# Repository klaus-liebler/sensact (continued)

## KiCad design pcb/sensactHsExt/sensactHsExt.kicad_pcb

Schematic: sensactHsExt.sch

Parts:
C1, C3, C4, C5, C6, C7, C8, C10, C12, C14, C16, C17: u1; C_0805_2012Metric_Pad1.15x1.40mm_HandSolder
C2, C9: 4u7; C_1206_3216Metric_Pad1.42x1.75mm_HandSolder
C11, C15: C; C_0805_2012Metric_Pad1.15x1.40mm_HandSolder
C13: m1; C_1206_3216Metric_Pad1.42x1.75mm_HandSolder
D1: LED; LED_0805_2012Metric_Pad1.15x1.40mm_HandSolder
D2: MBR0540; D_SOD-123
J1: B3; TestPoint_Pad_2.5x2.5mm
J2: LINKS1; PhoenixContact_MC_0,5_8-G-2.5_1x08_P2.50mm_Horizontal
J3, J7: SO8; SO-8_3.9x4.9mm_P1.27mm
J4: SensactBusConnector; IDC-Header_2x05_P2.54mm_Horizontal
J5: PROG; USB_Micro-B_Tensility_54-00023_Vertical
J6: LINKS2; PhoenixContact_MC_0,5_8-G-2.5_1x08_P2.50mm_Horizontal
J8: USB_C_Receptacle_USB2.0; USB_C_Receptacle_HRO_TYPE-C-31-M-12
J9: B4; TestPoint_Pad_2.5x2.5mm
J10: B5; TestPoint_Pad_2.5x2.5mm
J11: B6; TestPoint_Pad_2.5x2.5mm
J12: B7; TestPoint_Pad_2.5x2.5mm
J13: A15; TestPoint_Pad_2.5x2.5mm
J14: Conn_01x04; PhoenixContact_MC_0,5_4-G-2.5_1x04_P2.50mm_Horizontal
J15: P0A; TestPoint_Pad_2.5x2.5mm
J16: P0W; TestPoint_Pad_2.5x2.5mm
J17: P0B; TestPoint_Pad_2.5x2.5mm
J18: P1A; TestPoint_Pad_2.5x2.5mm
J19: P1W; TestPoint_Pad_2.5x2.5mm
J20: P1B; TestPoint_Pad_2.5x2.5mm
JP1: 3V3_INT; SolderJumper-2_P1.3mm_Open_Pad1.0x1.5mm
L1: 150u; L_Wuerth_HCI-7040
R1, R10, R12, R15, R16: R; R_0805_2012Metric_Pad1.15x1.40mm_HandSolder
R2: 10r; R_0805_2012Metric_Pad1.15x1.40mm_HandSolder
R3, R13: 3k3; R_0805_2012Metric_Pad1.15x1.40mm_HandSolder
R4: 2k2; R_0805_2012Metric_Pad1.15x1.40mm_HandSolder
R5, R6: 5k1; R_0805_2012Metric_Pad1.15x1.40mm_HandSolder
R7, R8, R9, R11, R14: 1k; R_0805_2012Metric_Pad1.15x1.40mm_HandSolder
R17: 10k; R_0805_2012Metric_Pad1.15x1.40mm_HandSolder
SW1: Reset; SW_SPST_CK_RS282G05A3
SW2: SW_Push; SW_Tactile_SPST_Angled_PTS645Vx83-2LFS
SW3: Mitsumi_SIQ-02FVS3
U1: FP-096H09A; FPC_TOP_1x08-1MP_P0.50mm_Horizontal
U2: STM32F072C8Tx; LQFP-48_7x7mm_P0.5mm_handsolder
U3: LMR14206; SOT-23-6
U4: SN65HVD230; SOIC-8_3.9x4.9mm_Pitch1.27mm_handsolder
U5: MCP42010; SOIC-14_3.9x8.7mm_P1.27mm_handsolder
Z9, Z10, Z11, Z12, Z13, Z14, Z15, Z16, Z17, Z18, Z19, Z20, Z21, Z22, Z23, Z24, Z25, Z26, Z27, Z28, Z29, Z30, Z31, Z32, Z33, Z34, Z35, Z36, Z37, Z38, Z39, Z40: StripRow3

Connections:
+3V3: C2.1, C3.1, C4.1, C5.1, C6.1, C7.1, C13.1, C14.1, C16.1, C17.1, JP1.2 (B), L1.1, R1.1, R7.1, R11.1, R12.2, R13.1, R15.1, U1.2 (VDD), U2.1 (VBAT), U2.9 (VDDA), U2.24 (VDD), U2.36 (VDDIO2), U2.48 (VDD), U4.3 (VCC), U5.12 (~SHDN), U5.14 (VDD); also elsewhere on the board
+24V: C9.1, J4.7 (24V), J4.8 (24V), J14.1, U3.5 (VIN); also elsewhere on the board
/CANH: J14.3, U4.7 (CANH)
/CANL: J14.4, U4.6 (CANL)
/CB: C12.2, U3.1 (CB)
/FB: R13.2, R14.1, U3.3 (FB)
/INT0: J4.4 (INT0), U2.19 (PB1)
/INT1: J4.5 (INT1), U2.18 (PB0)
/INT2: J4.6 (INT2), U2.14 (PA4)
/NRST: C1.1, SW1.1, U1.6 (~RESET), U2.7 (NRST), U5.11 (~RS)
/RX: J5.5 (GND), U2.31 (PA10)
/SCL: J4.2 (SCL), U2.21 (PB10)
/SDA: J4.3 (SDA), U2.22 (PB11)
/SW: C12.1, D2.1 (K), L1.2, U3.6 (SW)
/SWCLK: J5.1 (VBUS), U2.37 (PA14)
/SWDIO: J5.3 (D+), U2.34 (PA13)
/TX: J5.4 (ID), U2.30 (PA9)
/USB+: J8.A6 (D+), J8.B6 (D+), U2.33 (PA12)
/USB-: J8.A7 (D-), J8.B7 (D-), U2.32 (PA11)
CANR: U2.45 (PB8), U4.4 (R)
CANT: U2.46 (PB9), U4.1 (D)
GND: C1.2, C2.2, C3.2, C4.2, C5.2, C6.2, C7.2, C8.2, C9.2, C10.1, C11.2, C13.2, C14.2, C15.2, C16.2, C17.2, D2.2 (A), J4.9 (GND), J4.10 (GND), J5.2 (D-), J5.6 (Shield), J8.A1 (GND), J8.A12 (GND), J8.B1 (GND), J8.B12 (GND), J8.S1 (SHIELD), J14.2, R3.1, R5.1, R6.1, R14.2, R17.2, SW1.2, SW2.1, SW3.C, U1.7 (GND), U2.8 (VSSA), U2.23 (VSS), U2.35 (VSS), U2.44 (BOOT0), U2.47 (VSS), U3.2 (GND), U4.2 (GND), U5.4 (VSS); also elsewhere on the board
LCDBL: R2.2, U2.6 (PF1)
LCDCS: U1.1 (~CS), U2.16 (PA6)
LCDRS: U1.5 (RS), U2.13 (PA3)
LED: D1.1 (K), U2.12 (PA2)
unnamed: D1.2 (A), R1.2
unnamed: J1.1, U2.39 (PB3)
unnamed: J2.1, Z9.1
unnamed: J2.2, Z10.1
unnamed: J2.3, Z11.1
unnamed: J2.4, Z12.1
unnamed: J2.5, Z13.1
unnamed: J2.6, Z14.1
unnamed: J2.7, Z15.1
unnamed: J2.8, Z16.1
unnamed: J3.1, Z17.1
unnamed: J3.2, Z18.1
unnamed: J3.3, Z19.1
unnamed: J3.4, Z20.1
unnamed: J3.5, Z21.1
unnamed: J3.6, Z22.1
unnamed: J3.7, Z23.1
unnamed: J3.8, Z24.1
unnamed: J4.1 (3V3), JP1.1 (A)
unnamed: J6.1, Z25.1
unnamed: J6.2, Z26.1
unnamed: J6.3, Z27.1
unnamed: J6.4, Z28.1
unnamed: J6.5, Z29.1
unnamed: J6.6, Z30.1
unnamed: J6.7, Z31.1
unnamed: J6.8, Z32.1
unnamed: J7.1, Z33.1
unnamed: J7.2, Z34.1
unnamed: J7.3, Z35.1
unnamed: J7.4, Z36.1
unnamed: J7.5, Z37.1
unnamed: J7.6, Z38.1
unnamed: J7.7, Z39.1
unnamed: J7.8, Z40.1
unnamed: J8.A4 (VBUS), J8.A9 (VBUS), J8.B4 (VBUS), J8.B9 (VBUS), R4.2
unnamed: J8.A5 (CC1), R5.2
unnamed: J8.B5 (CC2), R6.2
unnamed: J9.1, U2.40 (PB4)
unnamed: J10.1, U2.41 (PB5)
unnamed: J11.1, U2.42 (PB6)
unnamed: J12.1, U2.43 (PB7)
unnamed: J13.1, U2.38 (PA15)
unnamed: J15.1, U5.8 (PA0)
unnamed: J16.1, U5.9 (PW0)
unnamed: J17.1, U5.10 (PB0)
unnamed: J18.1, U5.7 (PA1)
unnamed: J19.1, U5.6 (PW1)
unnamed: J20.1, U5.5 (PB1)
unnamed: R2.1, U1.8 (LEDA)
unnamed: R7.2, R8.2, SW2.2
unnamed: R10.1, R12.1, SW3.B
unnamed: R9.1, R11.2, SW3.A
unnamed: R15.2, R16.2, SW3.S
unnamed: R17.1, U4.8 (Rs)
ROTA: C10.2, R9.2, U2.11 (PA1)
ROTB: C11.1, R10.2, U2.10 (PA0)
ROTS: C15.1, R16.1, U2.20 (PB2)
S: C8.1, R8.1, U2.2 (PC13)
SPI2_CLK: U2.26 (PB13), U5.2 (SCK)
SPI2_CS_POTI: U2.25 (PB12), U5.1 (~CS)
SPI2_MOSI: U2.28 (PB15), U5.3 (SI)
SPI_CLK: U1.3 (SCL), U2.15 (PA5)
SPI_MOSI: U1.4 (SDA), U2.17 (PA7)
VBUS: R3.2, R4.1, U2.29 (PA8)

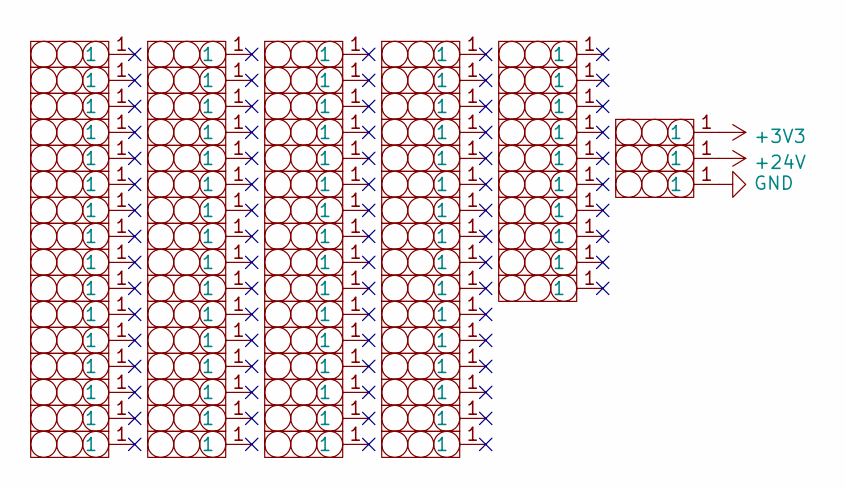
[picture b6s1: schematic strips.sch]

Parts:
Z3, Z4, Z5, Z41, Z42, Z43, Z44, Z45, Z46, Z47, Z48, Z49, Z50, Z51, Z52, Z53, Z54, Z55, Z56, Z57, Z58, Z59, Z60, Z61, Z62, Z63, Z64, Z65, Z66, Z67, Z68, Z69, Z70, Z71, Z72, Z73, Z74, Z75, Z76, Z77, Z78, Z79, Z80, Z81, Z82, Z83, Z84, Z85, Z86, Z87, Z88, Z89, Z90, Z91, Z92, Z93, Z94, Z95, Z96, Z97, Z98, Z99, Z100, Z101, Z102, Z103, Z104, Z105, Z106, Z107, Z108, Z109, Z110, Z111, Z112, Z113, Z114: StripRow3

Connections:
+3V3: Z3.1; also elsewhere on the board
+24V: Z4.1; also elsewhere on the board
GND: Z5.1; also elsewhere on the board

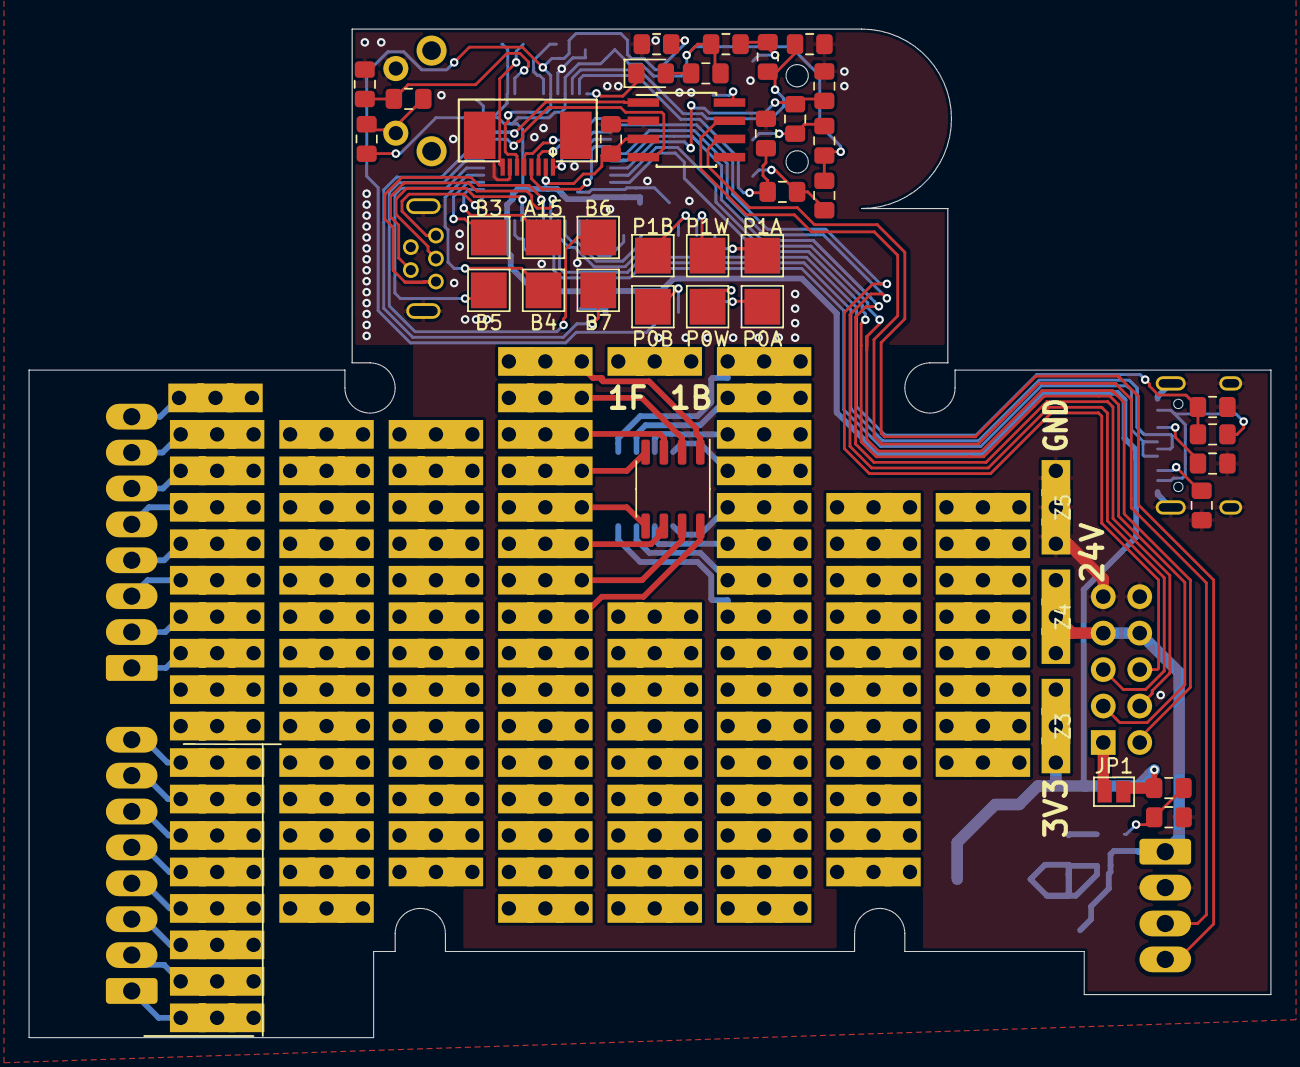
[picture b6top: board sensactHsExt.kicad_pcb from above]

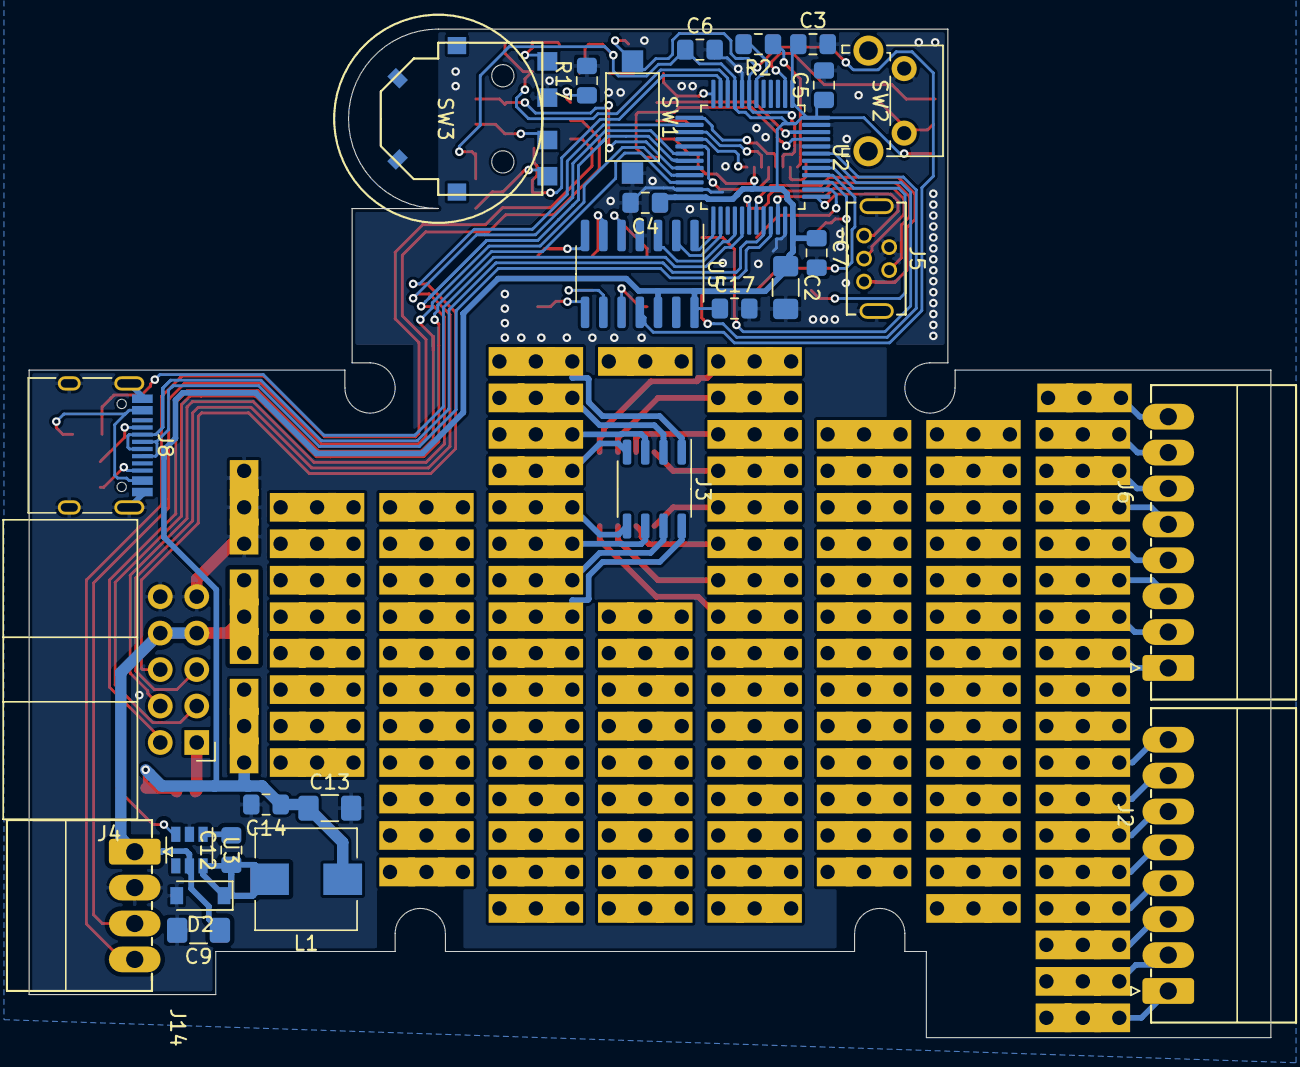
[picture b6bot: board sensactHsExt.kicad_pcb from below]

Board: 2 copper layers, 86.5 x 70.2 mm, 175 parts (28 on the bottom side), 91 nets.
